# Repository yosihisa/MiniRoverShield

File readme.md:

# Cansat Shield for Arduino Nano 33  
Arduino Nano 33 BLE Sense用のCanSatシールドです。    
これを使うことにより、簡単に小型ローバーを作ることができるようになります。  

# 搭載している機能  
標準的なCanSatに必要な以下の機能を搭載しています。  
・モーター  
・モータードライバ2つ  
・電池(Li-ion 10440)  
・電源回路  
・GNSSモジュール  
・microSD(データ記録用)  
・ニクロム線(パラシュート分離用)  
・MCU (Arduino nano 33内蔵)  
・地磁気センサ(Arduino nano 33内蔵)  
・通信機(Arduino nano 33内蔵)  

# 使い方
## 開発環境 
Arduino IDEを使用します。  
Arduino Nano 33 BLE Senseを使えるようにするためにいくつかのライブラリをインストールする必要があります。

1. Arduino IDEのボードマネージャで「Nano 33 BLE」と検索して「Arduino Mbed OS Nano Boards」をインストールします。
1. Arduino IDEのライブラリマネージャで「Nano 33 BLE」と検索して以下のライブラリをインストールします。 
  - **ArduinoBLE** (BLE通信用)
  - **Arduino_APDS9960** (ジェスチャ,明るさ,近接センサ用)
  - **Arduino_HTS221** (温度,湿度センサ用)
  - **Arduino_LPS22HB** (気圧センサ用)
  - **Arduino_LSM9DS1** (9軸センサ用)
## 動作確認
Arduino Nano 33 BLE Senseに搭載されているセンサの動作確認は各ライブラリのsample sketchを使用してください。  
MiniRoverShieldの動作確認は `/sketch` 以下の`test_`から始まるsketchを使用してください。

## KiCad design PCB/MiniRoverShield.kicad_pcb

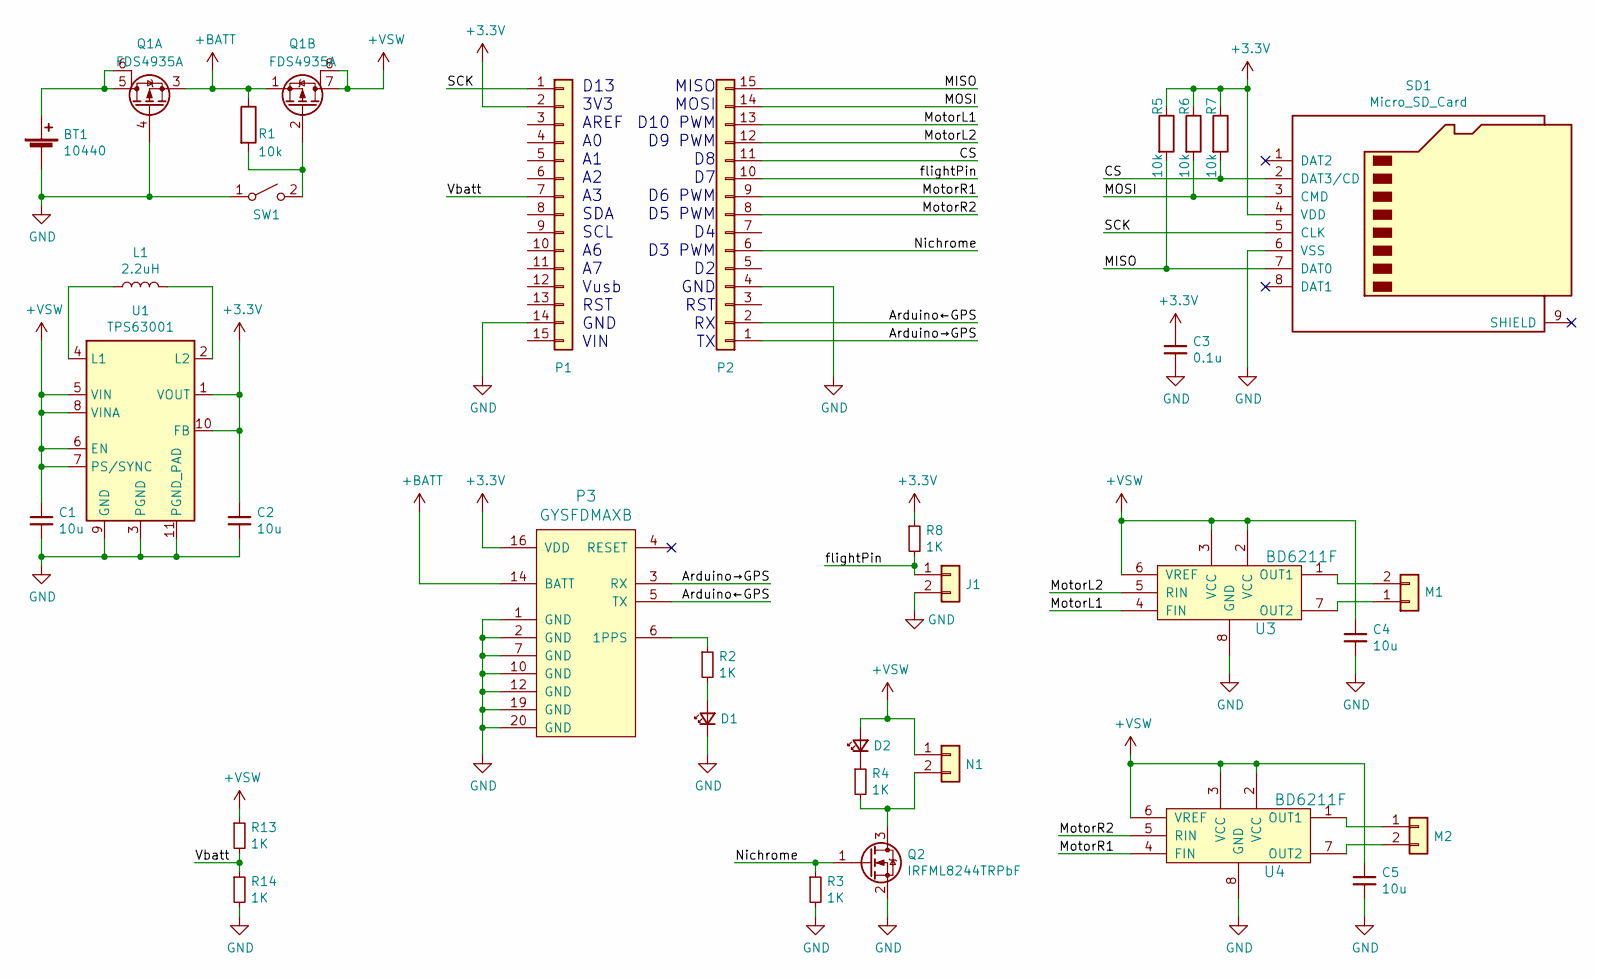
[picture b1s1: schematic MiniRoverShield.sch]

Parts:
BT1: 10440; BC-0402_AAA
C1, C2, C4, C5: 10u; C_0805_2012Metric_Pad1.15x1.40mm_HandSolder
C3: 0.1u; C_0603_1608Metric_Pad1.05x0.95mm_HandSolder
D1, D2: RED; LED_0603_1608Metric_Castellated
J1: flightPin; PinHeader_1x02_P2.54mm_Horizontal
L1: 2.2uH; TDK_VLS3012
M1, M2: Motor; JST_EH_B02B-EH-A_1x02_P2.50mm_Vertical
N1: Nichrome; MPT0.5_2-2.54
P1, P2: Arduino nano 33; PinSocket_1x15_P2.54mm_Vertical
P3: GYSFDMAXB
Q1: FDS4935A; SOIC-8_3.9x4.9mm_P1.27mm
Q2: IRFML8244TRPbF; SOT-23
R1, R5, R6, R7: 10k; R_0603_1608Metric_Pad1.05x0.95mm_HandSolder
R2, R3, R4, R8, R13, R14: 1K; R_0603_1608Metric_Pad1.05x0.95mm_HandSolder
SD1: Micro_SD_Card; microSD_HC_Hirose_DM3AT-SF-PEJM5
SW1: Power; SS-12D01-VG4
U1: TPS63001; Texas_S-PVSON-N10_ThermalVias
U3, U4: BD6211F; SOIC-8_3.9x4.9mm_P1.27mm

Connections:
+3V3: C2.1, C3.1, P1.2, P3.16 (VDD), R5.1, R6.1, R7.1, R8.1, SD1.4 (VDD), U1.1 (VOUT), U1.10 (FB)
+BATT: P3.14 (BATT), Q1.1 (S), Q1.3 (S), R1.1
+VSW: C1.1, C4.1, C5.1, D2.2 (A), N1.1, Q1.7 (D), Q1.8 (D), R13.1, U1.5 (VIN), U1.6 (EN), U1.7 (PS/SYNC), U1.8 (VINA), U3.2 (VCC), U3.3 (VCC), U3.6 (VREF), U4.2 (VCC), U4.3 (VCC), U4.6 (VREF)
/Arduino←GPS: P2.2, P3.5 (TX)
/Arduino→GPS: P2.1, P3.3 (RX)
/CS: P2.11, R7.2, SD1.2 (DAT3/CD)
/MISO: P2.15, R5.2, SD1.7 (DAT0)
/MOSI: P2.14, R6.2, SD1.3 (CMD)
/MotorL1: P2.13, U3.4 (FIN)
/MotorL2: P2.12, U3.5 (RIN)
/MotorR1: P2.9, U4.4 (FIN)
/MotorR2: P2.8, U4.5 (RIN)
/Nichrome: P2.6, Q2.1 (G), R3.1
/SCK: P1.1, SD1.5 (CLK)
/Vbatt: P1.7, R13.2, R14.1
/flightPin: J1.1, P2.10, R8.2
GND: BT1.2 (-), C1.2, C2.2, C3.2, C4.2, C5.2, D1.1 (K), J1.2, P1.14, P2.4, P3.1 (GND), P3.2 (GND), P3.7 (GND), P3.10 (GND), P3.12 (GND), P3.19 (GND), P3.20 (GND), Q1.4 (G), Q2.2 (S), R3.2, R14.2, SD1.6 (VSS), SW1.1 (A), U1.3 (PGND), U1.9 (GND), U1.11 (PGND_PAD), U3.8 (GND), U4.8 (GND)
unnamed: BT1.1 (+), Q1.5 (D), Q1.6 (D)
unnamed: D1.2 (A), R2.2
unnamed: D2.1 (K), R4.1
unnamed: L1.1, U1.4 (L1)
unnamed: L1.2, U1.2 (L2)
unnamed: M1.1, U3.7 (OUT2)
unnamed: M1.2, U3.1 (OUT1)
unnamed: M2.1, U4.1 (OUT1)
unnamed: M2.2, U4.7 (OUT2)
unnamed: N1.2, Q2.3 (D), R4.2
unnamed: P3.6 (1PPS), R2.1
unnamed: Q1.2 (4G), R1.2, SW1.2 (B)

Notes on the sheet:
D13 3V3 AREF A0 A1 A2 A3 SDA SCL A6 A7 Vusb RST GND VIN
MISO MOSI D10 PWM D9 PWM D8 D7 D6 PWM D5 PWM D4 D3 PWM D2 GND RST RX TX

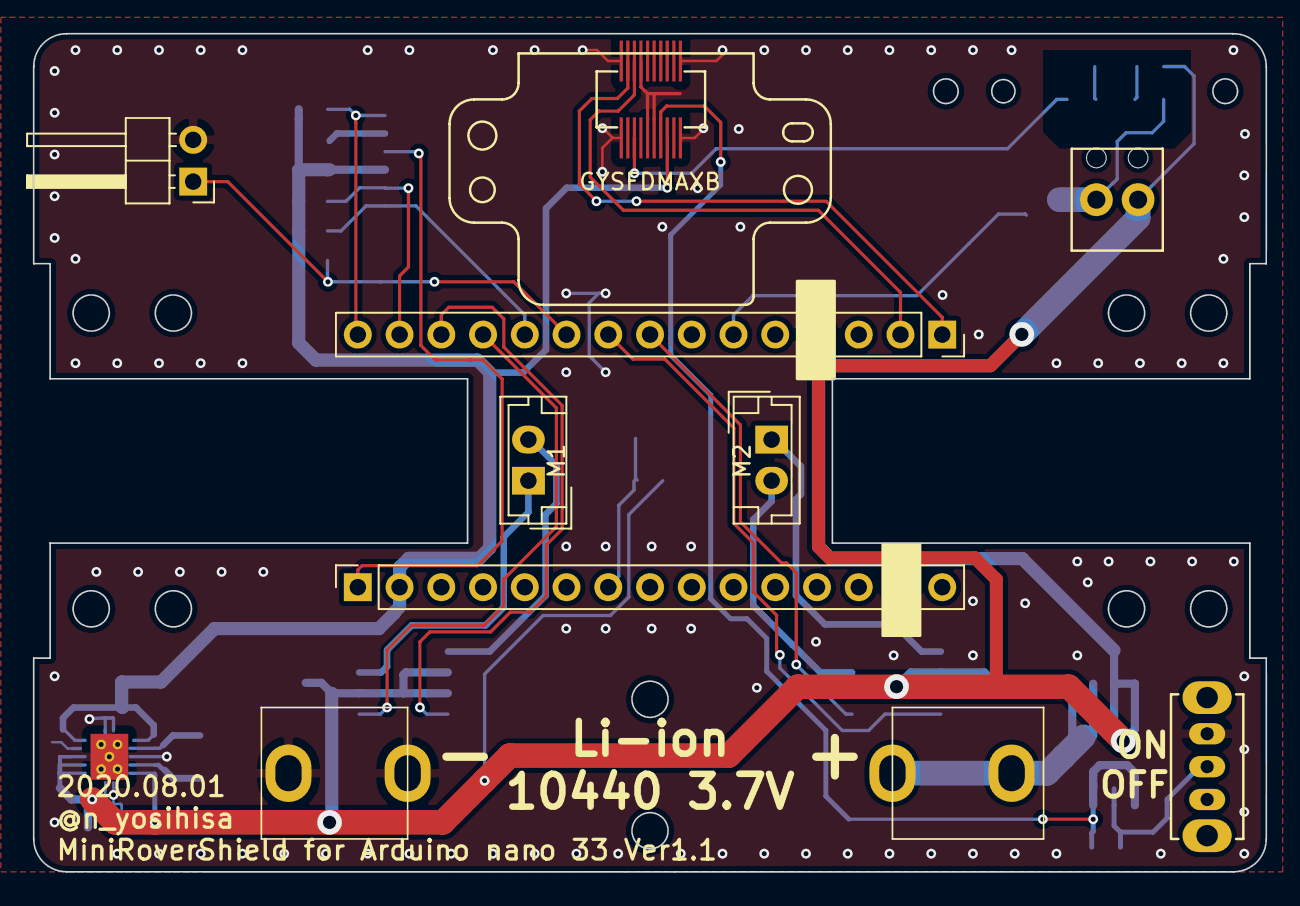
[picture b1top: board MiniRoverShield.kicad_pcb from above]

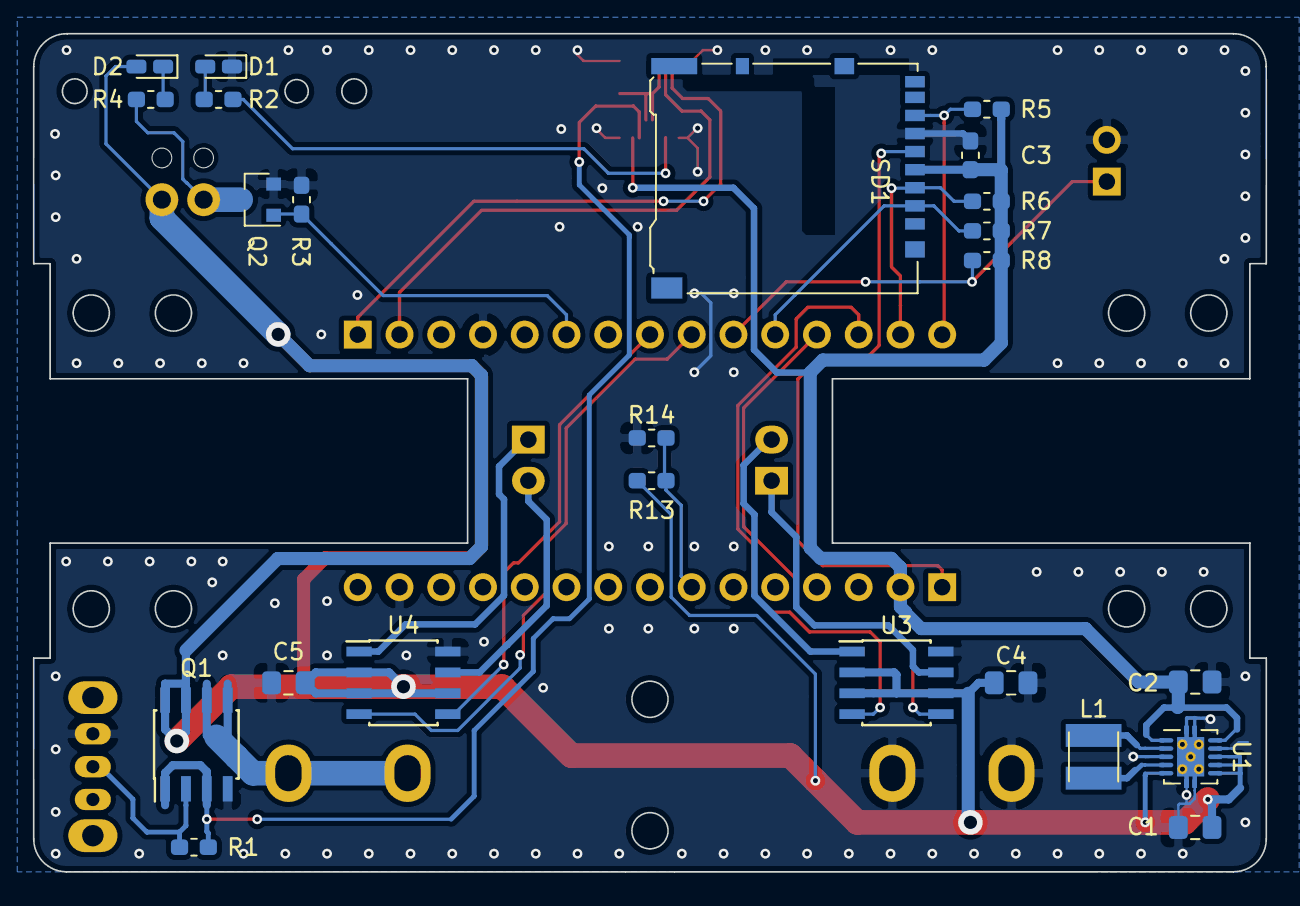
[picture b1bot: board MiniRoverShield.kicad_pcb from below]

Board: 2 copper layers, 75.0 x 51.0 mm, 33 parts (24 on the bottom side), 29 nets.

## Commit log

2019-07-28 Add PCB
    回路図作成
    基板 外形と部品配置まで
2019-08-03 配線完了
2019-08-03 Add Silk
2019-08-03 Add Gerber
2019-09-24 Add LICENSE
2020-02-11 Add test program
2020-02-11 Remove Line Trace
2020-02-12 Update LICENSE
2020-02-21 Gerber Update
2020-07-31 Change inductor
    VLF4012AT-2R2をVLS3012HBX-2R2Mに変更
2020-12-09 FET裏のパターン修正
2020-12-09 コメント追加
2021-04-12 imported to altium. 1st commit.
2021-04-13 Fixed a lot of major design error for ASSY.
2021-05-11 1st revision of reworked AW.
2022-01-28 Add STL files
